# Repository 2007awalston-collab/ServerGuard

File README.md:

# ServerGuard

An environmental monitoring shield for the Arduino Uno. It watches temperature and humidity and gives a visual and audible warning when conditions drift out of range. It's built for spaces like server rooms, where heat and moisture damage equipment.

I designed the schematic and the 2-layer PCB in KiCad 9.

## Features

- **Two sensors:** a DHT11 reads temperature and humidity, and an LM35 analog sensor gives a second temperature reading.
- **Status LEDs:** a green LED for normal conditions, plus separate yellow (warning) and red (alert) LEDs for temperature and for humidity.
- **Buzzer:** sounds an audible alarm.
- **Shield form factor:** the board stacks directly on an Arduino Uno R3, using the Uno's mounting holes. It takes power from the Uno's 5V rail.

## Hardware

| Ref | Part | Purpose |
|-----|------|---------|
| A1 | Arduino Uno R3 | Microcontroller (the shield mounts on it) |
| U1 | DHT11 | Temperature and humidity sensor |
| U3 | LM35 (SOIC-8) | Analog temperature sensor |
| D1 | Green LED | System normal |
| D2 / D3 | Yellow / red LED | Temperature warning / alert |
| D4 / D5 | Yellow / red LED | Humidity warning / alert |
| BZ1 | Buzzer (12 mm) | Audible alarm |
| R2–R7 | 220 Ω resistors | Current limiting for the LEDs and buzzer |

### Pin map

| Arduino pin | Connected to |
|-------------|--------------|
| A1 | DHT11 data |
| A2 | LM35 output |
| D8 | Yellow LED (humidity) |
| D9 | Red LED (humidity) |
| D10 | Yellow LED (temperature) |
| D11 | Red LED (temperature) |
| D12 | Green LED (normal) |
| D13 | Buzzer |
| 5V / GND | Sensor power |

## Schematic

## Prototype

Before designing the PCB, the team built and simulated the circuit in Tinkercad. Tinkercad has no DHT11, so the prototype used a TMP36 for temperature and a soil moisture sensor as the humidity input.

### Firmware

I wrote the prototype firmware: [`prototype/serverguard_tinkercad/serverguard_tinkercad.ino`](prototype/serverguard_tinkercad/serverguard_tinkercad.ino). In a continuous loop, it:

1. Reads the temperature and moisture sensors and prints both to the serial monitor (9600 baud).
2. Compares the readings against server-room style thresholds:

   | Reading | Warning (yellow LED) | Alarm (red LED + buzzer) |
   |---------|----------------------|--------------------------|
   | Temperature | 27 °C | 30 °C |
   | Moisture (raw ADC) | 350 | 500 |

3. Lights the green LED only when both readings are normal, and beeps the buzzer twice whenever either reading reaches its alarm level.

The LED and buzzer pins match the PCB. To run on the PCB's sensors, the firmware needs two changes: read the DHT11 with a DHT library, and convert the LM35 with `voltage × 100` instead of the TMP36's `(voltage − 0.5) × 100`.

## PCB

- 2 layers, about 82 × 88 mm
- +5V copper pour on the top layer and a GND pour on the bottom layer
- Through-hole LEDs, resistors and buzzer for easy hand assembly. The LM35 is surface-mount (SOIC-8).

## Repository contents

| File | Contents |
|------|----------|
| `ECCSEgroup7.kicad_pro` | KiCad project file |
| `ECCSEgroup7.kicad_sch` | Schematic |
| `ECCSEgroup7.kicad_pcb` | PCB layout |
| `prototype/serverguard_tinkercad/` | Arduino firmware from the Tinkercad prototype |
| `images/` | 3D render, schematic, PCB layout and Tinkercad prototype |

To view the design, open `ECCSEgroup7.kicad_pro` in KiCad 9 or later.

## My role

This was a four-person team project for a college engineering course. I led the team, designed the schematic and PCB layout, wrote the Arduino firmware and authored most of the presentation and the final report. My teammates came up with the initial concept and helped with brainstorming, Tinkercad prototyping and the presentation.

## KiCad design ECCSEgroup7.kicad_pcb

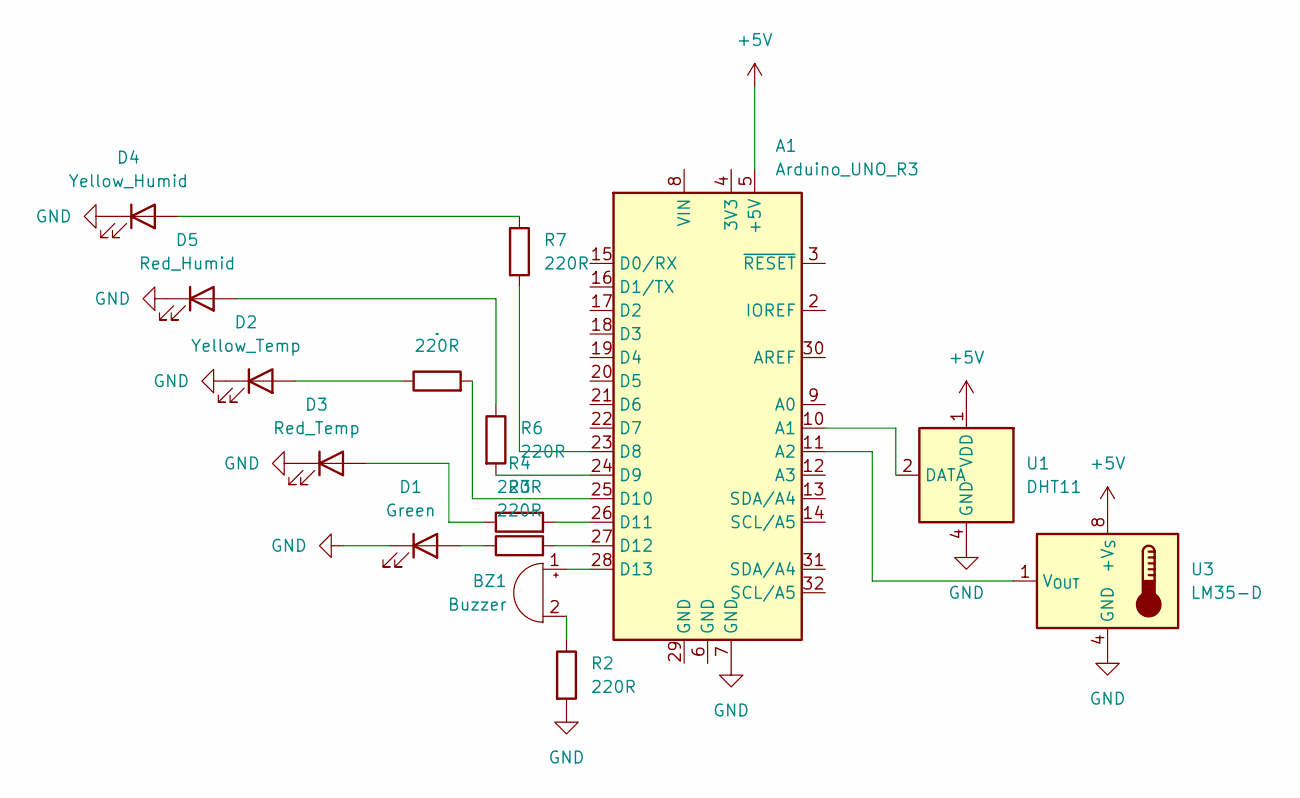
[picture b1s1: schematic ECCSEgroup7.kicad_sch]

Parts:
A1: Arduino_UNO_R3; Arduino_UNO_R3_WithMountingHoles
BZ1: Buzzer; Buzzer_12x9.5RM7.6
D1: Green; LED_D3.0mm
D2: Yellow_Temp; LED_D3.0mm
D3: Red_Temp; LED_D3.0mm
D4: Yellow_Humid; LED_D3.0mm
D5: Red_Humid; LED_D3.0mm
R2, R3, R4, R5, R6, R7: 220R; R_Axial_DIN0207_L6.3mm_D2.5mm_P7.62mm_Horizontal
U1: DHT11; Aosong_DHT11_5.5x12.0_P2.54mm
U3: LM35-D; SOIC-8_3.9x4.9mm_P1.27mm

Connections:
+5V: A1.5 (+5V), U1.1 (VDD), U3.8 (+V_{S})
GND: A1.7 (GND), D1.1 (K), D2.1 (K), D3.1 (K), D4.1 (K), D5.1 (K), R2.2, U1.4 (GND), U3.4 (GND)
unnamed: A1.10 (A1), U1.2 (DATA)
unnamed: A1.11 (A2), U3.1 (V_{OUT})
unnamed: A1.23 (D8), R7.2
unnamed: A1.24 (D9), R6.2
unnamed: A1.25 (D10), R5.2
unnamed: A1.26 (D11), R4.2
unnamed: A1.27 (D12), R3.2
unnamed: A1.28 (D13), BZ1.1 (+)
unnamed: BZ1.2 (-), R2.1
unnamed: D1.2 (A), R3.1
unnamed: D2.2 (A), R5.1
unnamed: D3.2 (A), R4.1
unnamed: D4.2 (A), R7.1
unnamed: D5.2 (A), R6.1

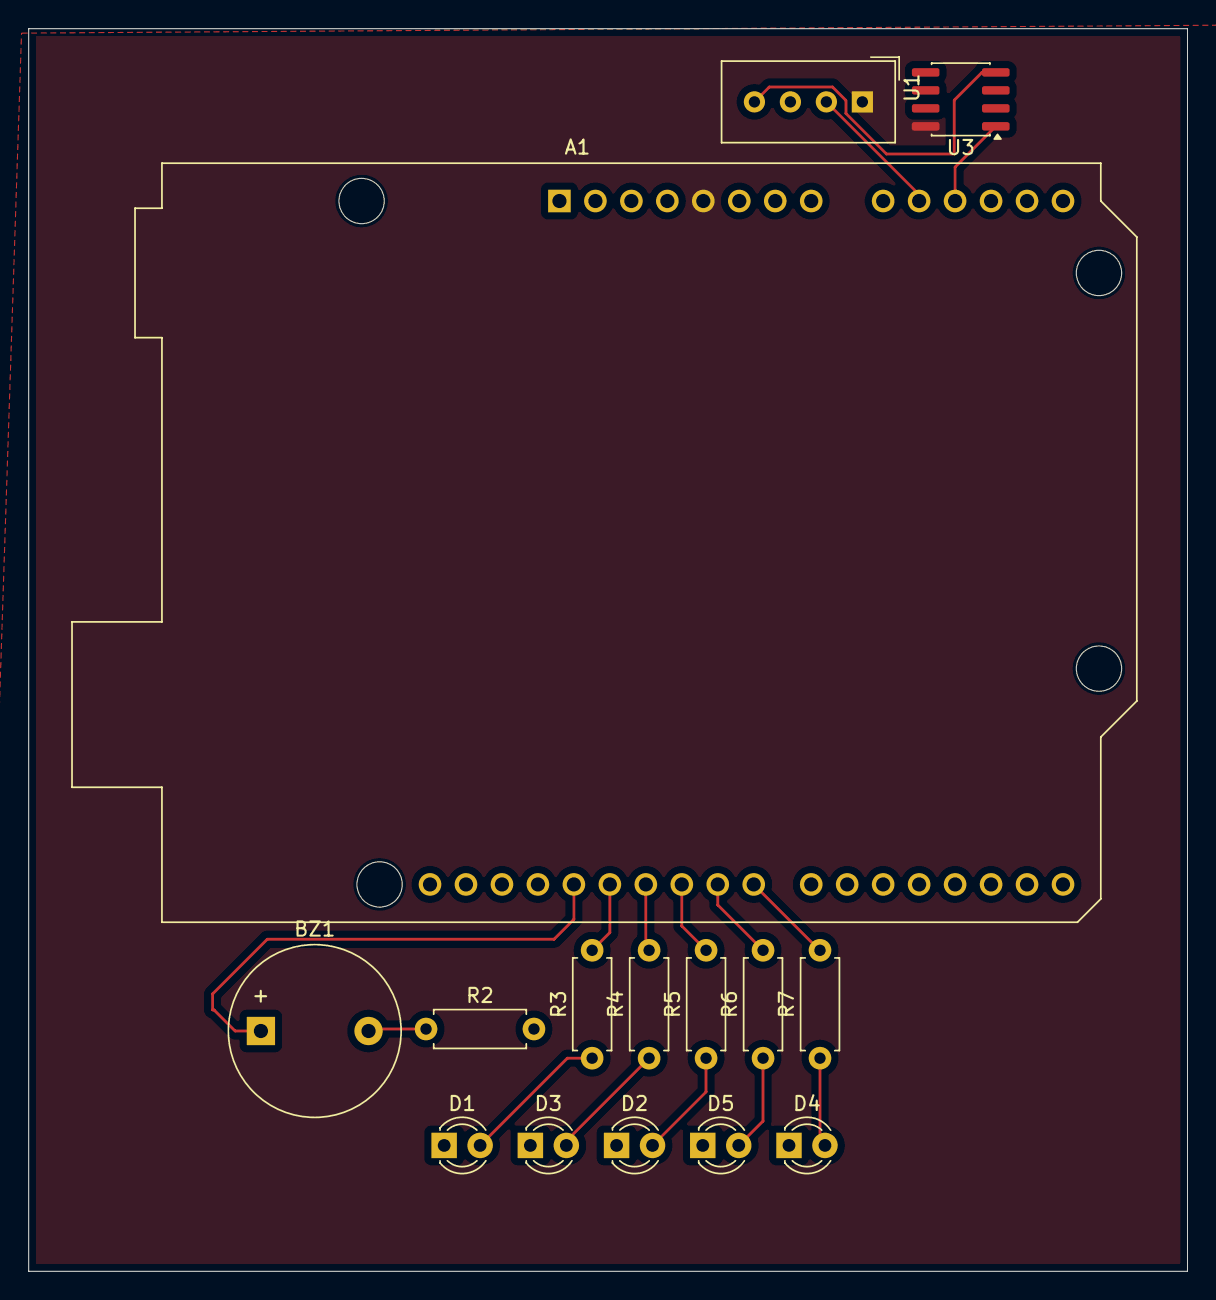
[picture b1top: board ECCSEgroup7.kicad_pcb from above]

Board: 2 copper layers, 81.8 x 87.8 mm, 15 parts (0 on the bottom side), 16 nets.
